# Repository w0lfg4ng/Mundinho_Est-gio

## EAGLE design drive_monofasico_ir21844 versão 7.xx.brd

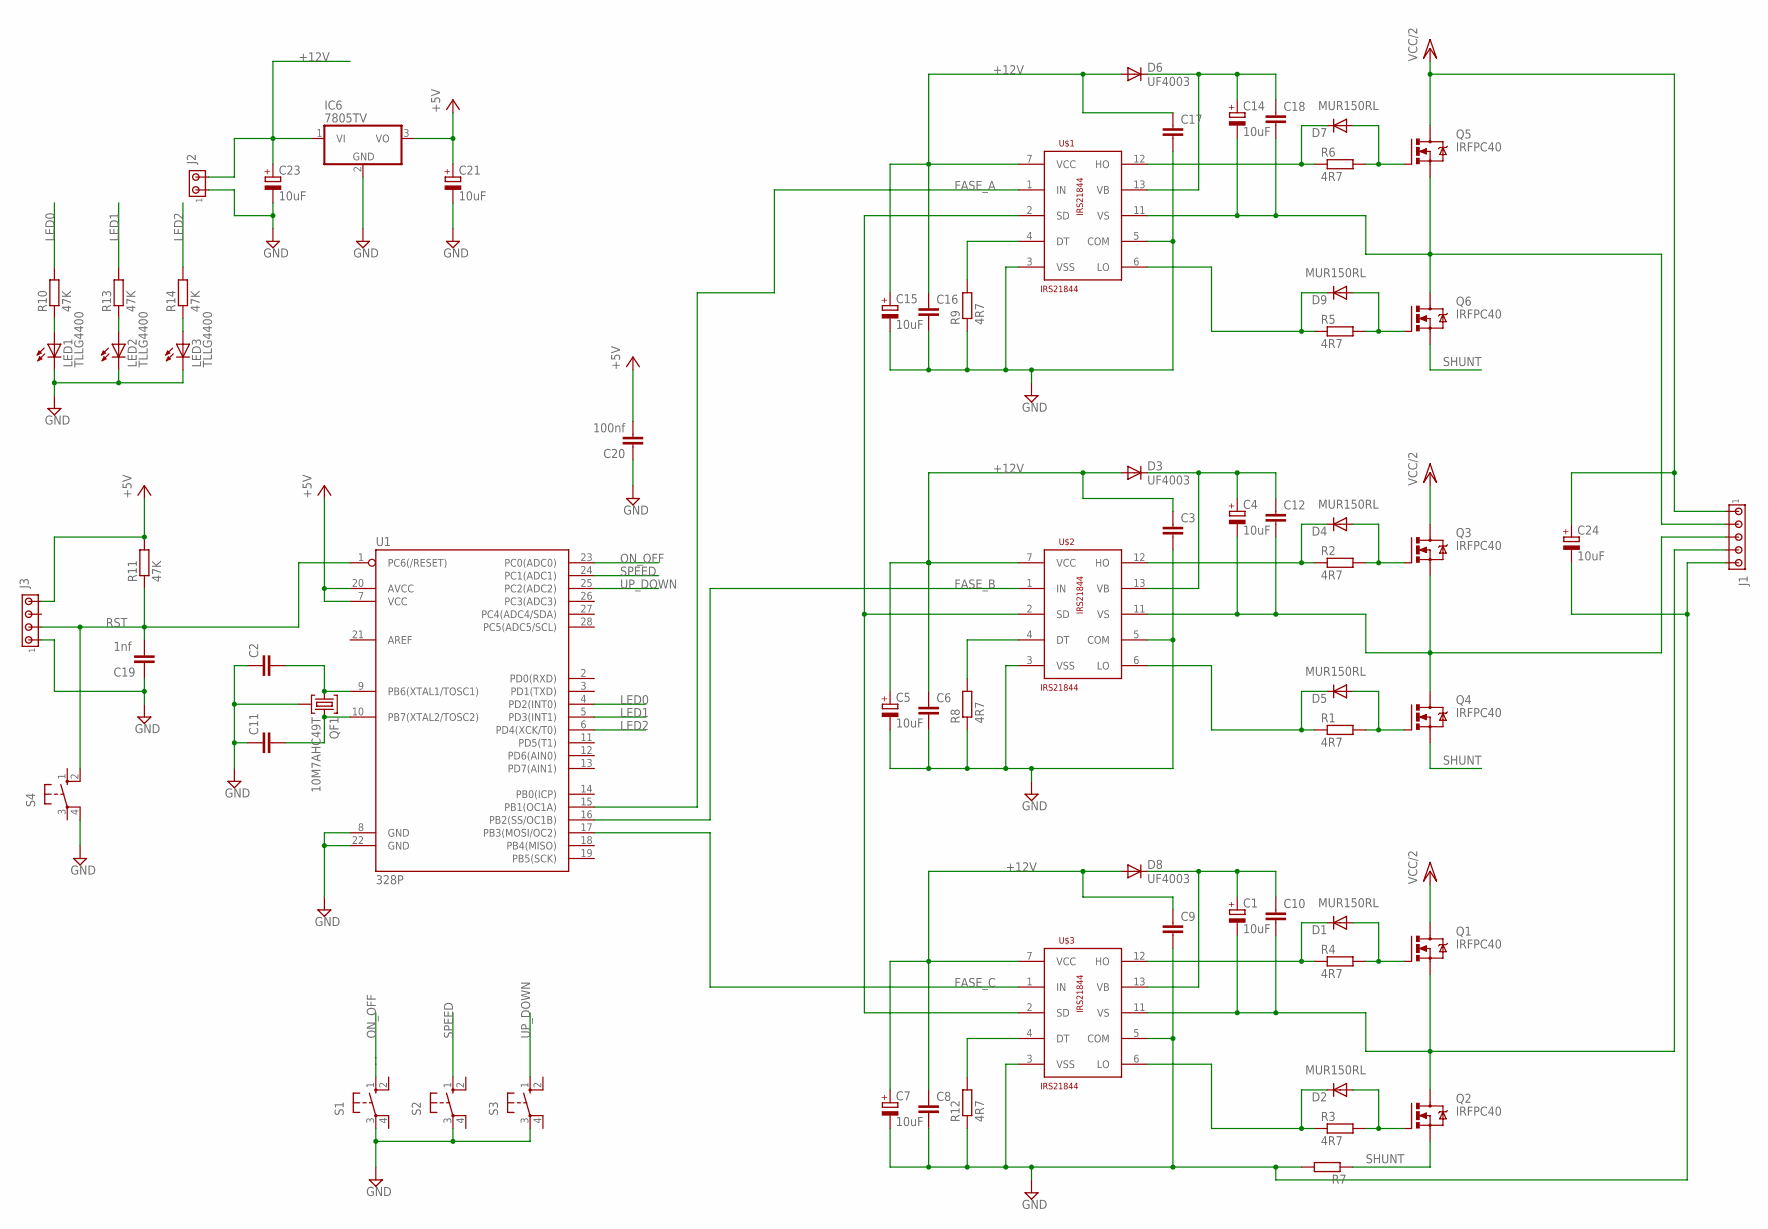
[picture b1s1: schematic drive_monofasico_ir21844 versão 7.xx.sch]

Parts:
C1, C4, C5, C7, C14, C15, C21, C23, C24: 10uF; E5-6
C2, C3, C6, C8, C9, C10, C11, C12, C16, C17, C18: C7.5/3; C7.5B3
C19: 1nf; C050-025X075
C20: 100nf; C050-025X075
D1, D2, D4, D5, D7, D9: MUR150RL; DO41-10
D3, D6, D8: UF4003; DO41-10
IC6: 7805TV; TO220V
J1: MTA05-156; 1X5MTA
J2: MTA02-100; 10X02MTA
J3: MTA04-100; 10X04MTA
LED1, LED2, LED3: TLLG4400; LED3MM
Q1, Q2, Q3, Q4, Q5, Q6: IRFPC40; TO247BV
QF1: 10M7AHC49T; HC49U
R1, R2, R3, R4, R5, R6, R8, R9, R12: 4R7; 0207/12
R7: R-EU_0613/15; P0613/15
R10, R11, R13, R14: 47K; 0207/12
S1, S2, S3, S4: 10-XX; B3F-10XX
U1: 328P; DIP28
U$1, U$2, U$3: IRS21844

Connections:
+12V: C3.1, C5.+, C6.1, C7.+, C8.1, C9.1, C15.+, C16.1, C17.1, C23.+, D3.A, D6.A, D8.A, IC6.1 (VI), J2.2, U$1.7 (VCC), U$2.7 (VCC), U$3.7 (VCC)
+VCC: C20.2, C21.+, IC6.3 (VO), J3.4, R11.2, U1.7 (VCC), U1.20 (AVCC)
FASE_A: U1.15 (PB1(OC1A)), U$1.1 (IN)
FASE_B: U1.16 (PB2(SS/OC1B)), U$2.1 (IN)
FASE_C: U1.17 (PB3(MOSI/OC2)), U$3.1 (IN)
GND: C2.1, C3.2, C5.-, C6.2, C7.-, C8.2, C9.2, C11.1, C15.-, C16.2, C17.2, C19.2, C20.1, C21.-, C23.-, C24.-, IC6.2 (GND), J1.5, J2.1, J3.1, LED1.K (C), LED2.K (C), LED3.K (C), QF1.2, R7.2, R8.1, R9.1, R12.1, S1.3, S2.3, S3.3, S4.4 (P1), U1.8 (GND), U1.22 (GND), U$1.3 (VSS), U$1.5 (COM), U$2.3 (VSS), U$2.5 (COM), U$3.3 (VSS), U$3.5 (COM)
LED0: R10.2, U1.4 (PD2(INT0))
LED1: R13.2, U1.5 (PD3(INT1))
LED2: R14.2, U1.6 (PD4(XCK/T0))
unnamed: U$1.2 (SD), U$2.2 (SD), U$3.2 (SD)
unnamed: D1.A, Q1.G, R4.2
unnamed: D1.C, R4.1, U$3.12 (HO)
unnamed: D2.C, R3.1, U$3.6 (LO)
unnamed: D4.A, Q3.G, R2.2
unnamed: R9.2, U$1.4 (DT)
unnamed: D5.A, Q4.G, R1.2
unnamed: D4.C, R2.1, U$2.12 (HO)
unnamed: D5.C, R1.1, U$2.6 (LO)
unnamed: C2.2, QF1.1, U1.9 (PB6(XTAL1/TOSC1))
unnamed: C11.2, QF1.3, U1.10 (PB7(XTAL2/TOSC2))
unnamed: D2.A, Q2.G, R3.2
unnamed: LED1.A, R10.1
unnamed: LED2.A, R13.1
unnamed: D7.A, Q5.G, R6.2
unnamed: D9.A, Q6.G, R5.2
unnamed: D7.C, R6.1, U$1.12 (HO)
unnamed: D9.C, R5.1, U$1.6 (LO)
unnamed: LED3.A, R14.1
unnamed: C14.+, C18.1, D6.C, U$1.13 (VB)
unnamed: C14.-, C18.2, J1.2, Q5.S, Q6.D, U$1.11 (VS)
unnamed: R8.2, U$2.4 (DT)
unnamed: C4.-, C12.2, J1.3, Q3.S, Q4.D, U$2.11 (VS)
unnamed: C4.+, C12.1, D3.C, U$2.13 (VB)
unnamed: C1.-, C10.2, J1.4, Q1.S, Q2.D, U$3.11 (VS)
unnamed: C1.+, C10.1, D8.C, U$3.13 (VB)
unnamed: R12.2, U$3.4 (DT)
ON_OFF: S1.1 (S), U1.23 (PC0(ADC0))
RST: C19.1, J3.2, R11.1, S4.2 (S1), U1.1 (PC6(/RESET))
SHUNT: Q2.S, Q4.S, Q6.S, R7.1
SPEED: S2.1 (S), U1.24 (PC1(ADC1))
UP_DOWN: S3.1 (S), U1.25 (PC2(ADC2))
VCC/2: C24.+, J1.1, Q1.D, Q3.D, Q5.D

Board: 2 copper layers, 67 parts (0 on the bottom side), 42 nets, no tracks yet.
